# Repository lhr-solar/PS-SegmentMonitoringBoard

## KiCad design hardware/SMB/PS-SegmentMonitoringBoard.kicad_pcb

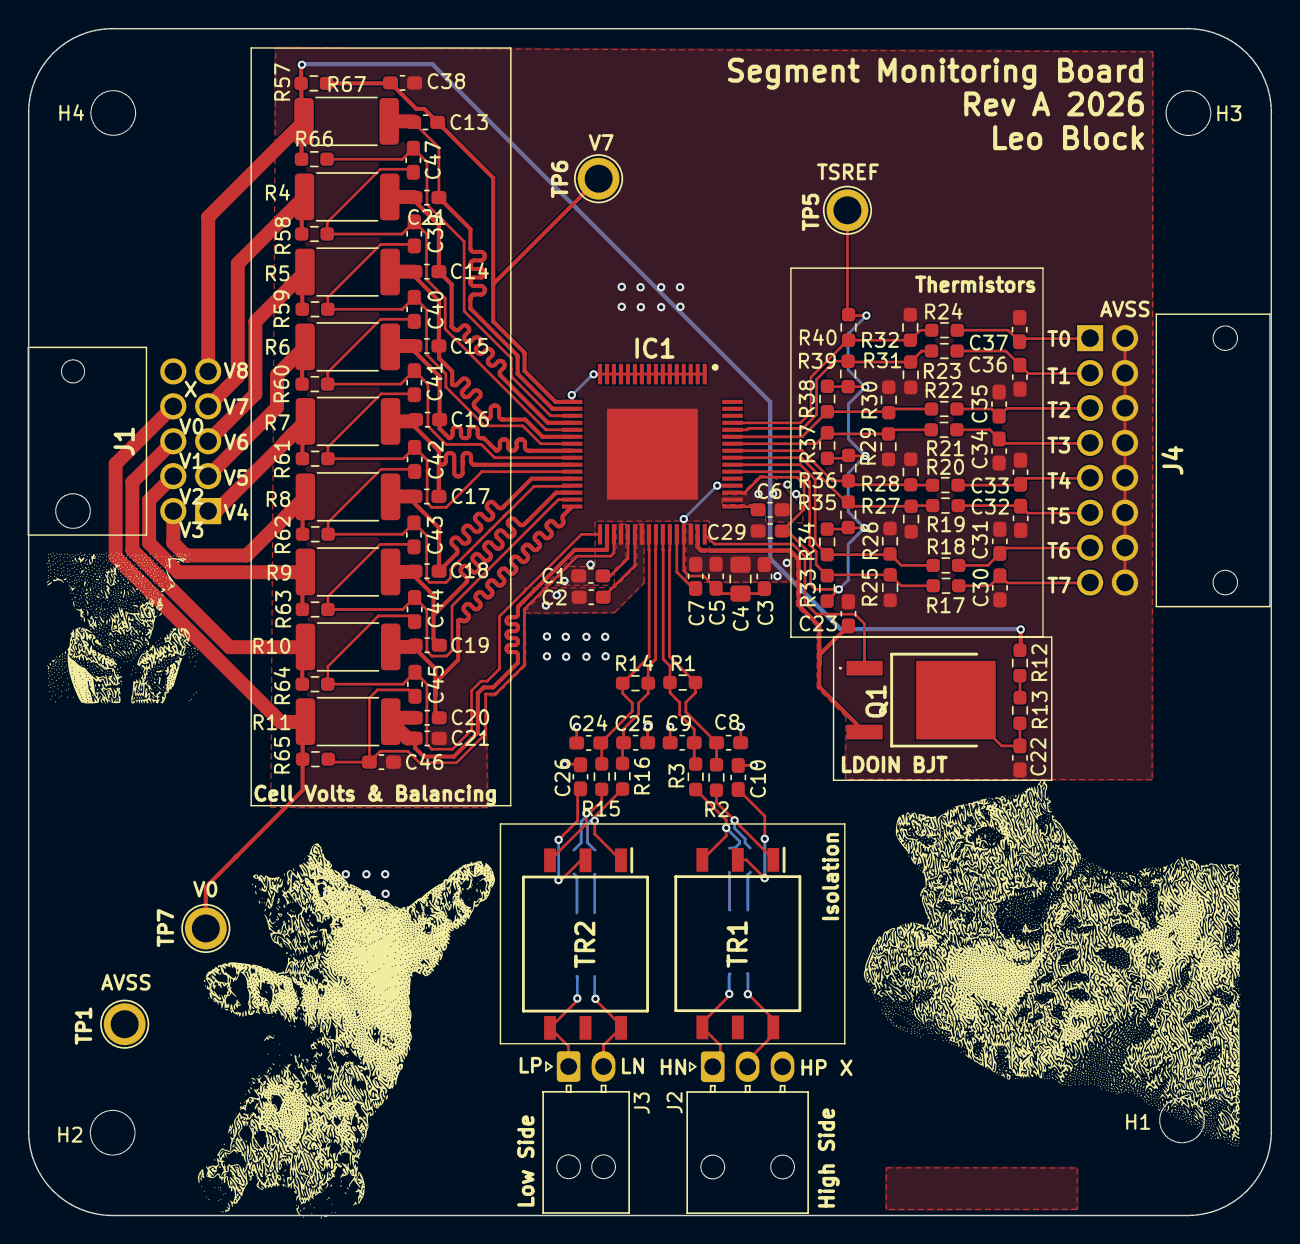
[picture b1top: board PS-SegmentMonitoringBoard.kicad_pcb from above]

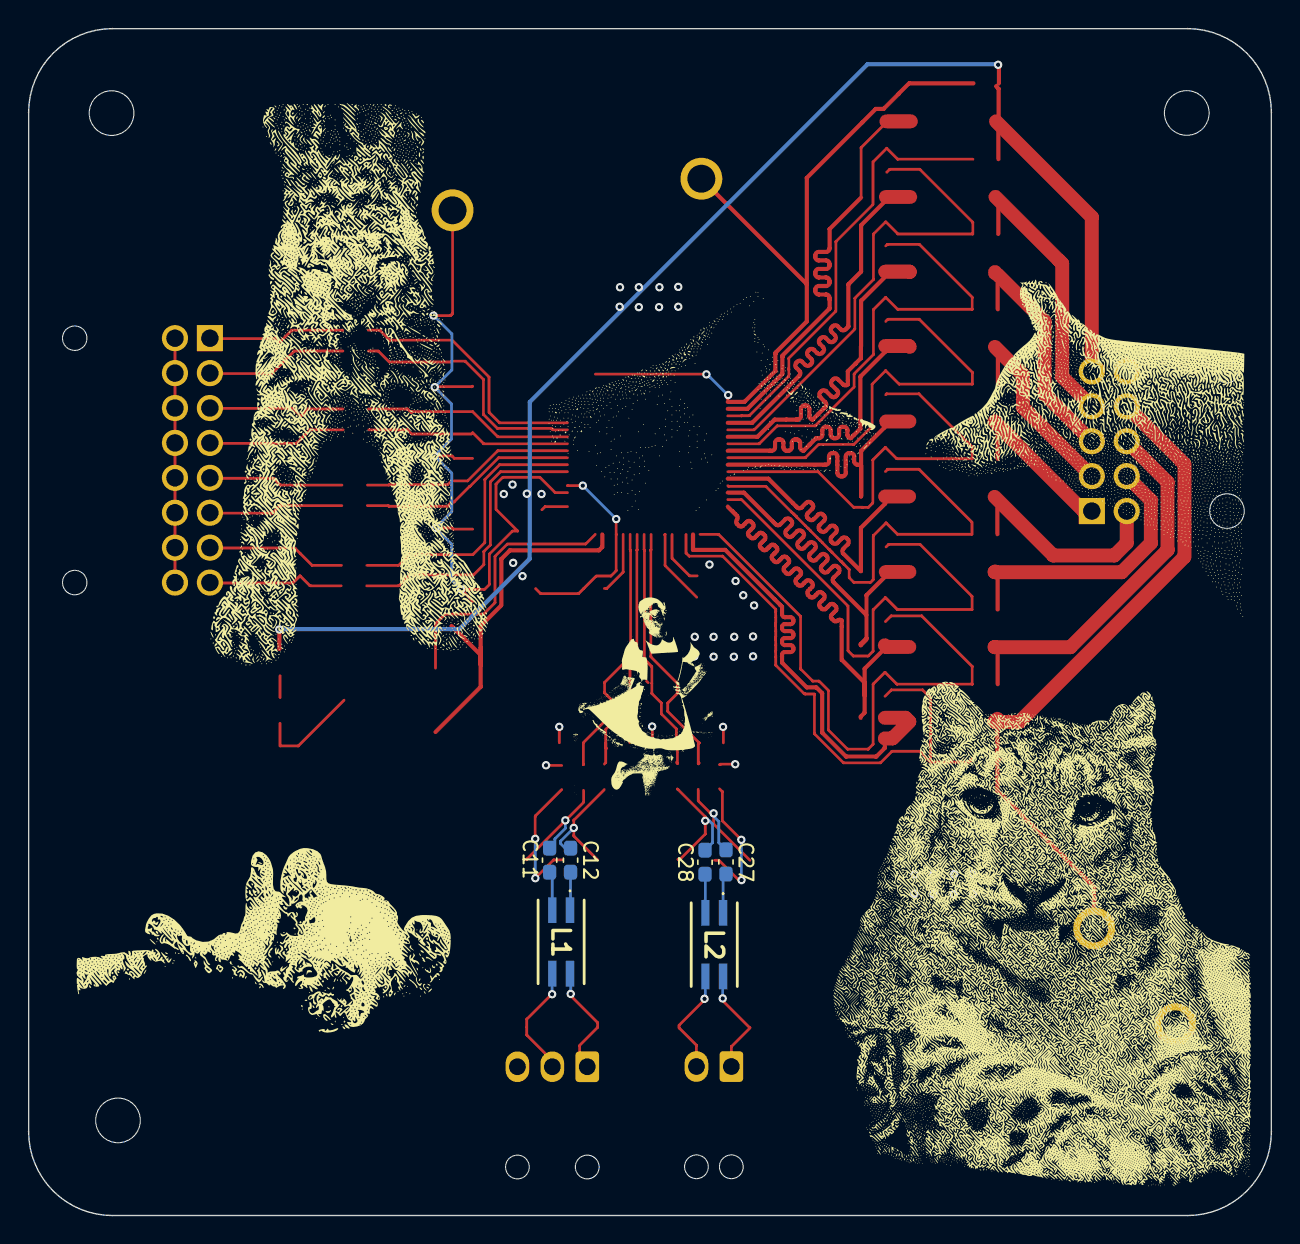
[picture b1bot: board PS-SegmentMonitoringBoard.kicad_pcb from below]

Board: 4 copper layers, 89.0 x 85.0 mm, 118 parts (6 on the bottom side), 73 nets.

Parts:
C1, C2, C29, C30, C31, C32, C33, C34, C35, C36, C37: 1uF; C_0603_1608Metric_Pad1.08x0.95mm_HandSolder
C3: 22nF; C_0603_1608Metric_Pad1.08x0.95mm_HandSolder
C4: 4.7uF; C_0805_2012Metric_Pad1.18x1.45mm_HandSolder
C5: 100nF; C_0603_1608Metric_Pad1.08x0.95mm_HandSolder
C6: 2.2uF; C_0603_1608Metric_Pad1.08x0.95mm_HandSolder
C7, C23: 0.1uF; C_0603_1608Metric_Pad1.08x0.95mm_HandSolder
C8, C9, C11, C12, C24, C25, C27, C28: 220pF; C_0603_1608Metric_Pad1.08x0.95mm_HandSolder
C10, C26: 100pF; C_0603_1608Metric_Pad1.08x0.95mm_HandSolder
C13, C14, C15, C16, C17, C18, C19, C20, C21, C21#2, C39, C40, C41, C42, C43, C44, C45, C46, C47: 0.47uF; C_0603_1608Metric_Pad1.08x0.95mm_HandSolder
C22: 0.22uF; C_0603_1608Metric_Pad1.08x0.95mm_HandSolder
C38: 10nF; C_0603_1608Metric_Pad1.08x0.95mm_HandSolder
H1, H2, H3, H4: MountingHole; MountingHole_3.2mm_M3
IC1: BQ79616PAPR; QFP50P1200X1200X120-65N
J1: voltTapConn; 1053141110
J2: highSideConn; Molex_Nano-Fit_105313-xx03_1x03_P2.50mm_Horizontal
J3: lowSideConn; Molex_Nano-Fit_105313-xx02_1x02_P2.50mm_Horizontal
J4: thermConn; 1053141116
L1, L2: L_Coupled_1423; 744242471
LOGO1: Dr. Hallock; LHRs_LOGO
Q1: ZXTN4004KTC
R1, R14, R17, R18, R19, R20, R21, R22, R23, R24: 1k; R_0603_1608Metric_Pad0.98x0.95mm_HandSolder
R2, R3, R15, R16: 49; R_0603_1608Metric_Pad0.98x0.95mm_HandSolder
R4, R5, R6, R7, R8, R9, R10, R11, R67: 6.2; R_2512_6332Metric_Pad1.40x3.35mm_HandSolder
R12: 200; R_0603_1608Metric_Pad0.98x0.95mm_HandSolder
R13, R58, R59, R60, R61, R62, R63, R64, R65, R66: 100; R_0603_1608Metric_Pad0.98x0.95mm_HandSolder
R25, R26, R27, R28, R29, R30, R31, R32: 15k; R_0603_1608Metric_Pad0.98x0.95mm_HandSolder
R33, R34, R35, R36, R37, R38, R39, R40: 3.6k; R_0603_1608Metric_Pad0.98x0.95mm_HandSolder
R57: 30; R_0603_1608Metric_Pad0.98x0.95mm_HandSolder
TP1: AVSS; TestPoint_Plated_Hole_D2.0mm
TP5: TSREF; TestPoint_Plated_Hole_D2.0mm
TP6: V7; TestPoint_Plated_Hole_D2.0mm
TP7: V0; TestPoint_Plated_Hole_D2.0mm
TR1, TR2: HMU1228NL; SOP254P1270X685-6N

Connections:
/CB0: C20.2, C21.1, IC1.34 (CB0), R11.2
/CB1: C19.2, C20.1, IC1.32 (CB1), R10.2
/CB2: C18.2, C19.1, IC1.30 (CB2), R9.2
/CB3: C17.2, C18.1, IC1.28 (CB3), R8.2
/CB4: C16.2, C17.1, IC1.26 (CB4), R7.2
/CB5: C15.2, C16.1, IC1.24 (CB5), R6.2
/CB6: C14.2, C15.1, IC1.22 (CB6), R5.2
/CB7: C14.1, C21#2.2, IC1.20 (CB7), R4.2
/CB8: C13.2, C21#2.1, IC1.18 (CB8), R67.2
/CVDD: C3.1, C4.1, C5.1, IC1.45 (CVDD), IC1.52 (RX)
/Cell_Balancing/V0: J1.9, R11.1, R65.1, TP7.1 (1_1)
/Cell_Balancing/V1: J1.8, R10.1, R64.1
/Cell_Balancing/V2: J1.7, R9.1, R63.1
/Cell_Balancing/V3: J1.6, R8.1, R62.1
/Cell_Balancing/V4: J1.5, R7.1, R61.1
/Cell_Balancing/V5: J1.4, R6.1, R60.1
/Cell_Balancing/V6: J1.3, R5.1, R59.1
/Cell_Balancing/V7: J1.2, R4.1, R58.1
/Cell_Balancing/V8: J1.1, R12.1, R57.2, R66.1, R67.1
/LDOIN_NPN/LDOIN: C23.1, IC1.47 (LDOIN), Q1.3 (E)
/LDOIN_NPN/NPNB: IC1.48 (NPNB), Q1.1 (B)
/TSREF: C29.1, IC1.51 (TSREF), R33.2, R34.2, R35.2, R36.2, R37.2, R38.2, R39.2, R40.2, TP5.1 (1_1)
/Thermistors/NTC0: IC1.61 (GPIO1), R24.1, R32.2, R40.1
/Thermistors/NTC1: IC1.60 (GPIO2), R23.1, R31.2, R39.1
/Thermistors/NTC2: IC1.59 (GPIO3), R22.1, R30.2, R38.1
/Thermistors/NTC3: IC1.58 (GPIO4), R21.1, R29.2, R37.1
/Thermistors/NTC4: IC1.57 (GPIO5), R20.1, R28.2, R36.1
/Thermistors/NTC5: IC1.56 (GPIO6), R19.1, R27.2, R35.1
/Thermistors/NTC6: IC1.55 (GPIO7), R18.1, R26.2, R34.1
/Thermistors/NTC7: IC1.54 (GPIO8), R17.1, R25.2, R33.1
/Thermistors/TEMP_0: C37.1, J4.8, R24.2
/Thermistors/TEMP_1: C36.1, J4.7, R23.2
/Thermistors/TEMP_2: C35.1, J4.6, R22.2
/Thermistors/TEMP_3: C34.1, J4.5, R21.2
/Thermistors/TEMP_4: C33.1, J4.4, R20.2
/Thermistors/TEMP_5: C32.1, J4.3, R19.2
/Thermistors/TEMP_6: C31.1, J4.2, R18.2
/Thermistors/TEMP_7: C30.1, J4.1, R17.2
/Volt_Taps/VC0: C45.2, C46.1, IC1.35 (VC0), R65.2
/Volt_Taps/VC1: C44.2, C45.1, IC1.33 (VC1), R64.2
/Volt_Taps/VC2: C43.2, C44.1, IC1.31 (VC2), R63.2
/Volt_Taps/VC3: C42.2, C43.1, IC1.29 (VC3), R62.2
/Volt_Taps/VC4: C41.2, C42.1, IC1.27 (VC4), R61.2
/Volt_Taps/VC5: C40.2, C41.1, IC1.25 (VC5), R60.2
/Volt_Taps/VC6: C39.2, C40.1, IC1.23 (VC6), R59.2
/Volt_Taps/VC7: C39.1, C47.2, IC1.21 (VC7), R58.2
/Volt_Taps/VC8: C47.1, IC1.19 (VC8), R66.2
/extraCells: C13.1, C38.2, IC1.1 (BAT), IC1.2 (CB16), IC1.3 (VC16), IC1.4 (CB15), IC1.5 (VC15), IC1.6 (CB14), IC1.7 (VC14), IC1.8 (CB13), IC1.9 (VC13), IC1.10 (CB12), IC1.11 (VC12), IC1.12 (CB11), IC1.13 (VC11), IC1.14 (CB10), IC1.15 (VC10), IC1.16 (CB9), IC1.17 (VC9), R57.1, TP6.1 (1_1)
/highSideIsolation/COMHN: C9.1, IC1.42 (COMHN), R1.2, R3.1
/highSideIsolation/COMHP: C8.1, IC1.43 (COMHP), R1.1, R2.1
/highSideIsolation/isolatedCOMHN: J2.1, L1.4, TR1.4
/highSideIsolation/isolatedCOMHP: J2.2, L1.3, TR1.6
/highSideIsolation/preIsolationCOMHN: C12.1, R3.2, TR1.3
/highSideIsolation/preIsolationCOMHP: C11.1, R2.2, TR1.1
/lowSideIsolation/COMLN: C25.1, IC1.41 (COMLN), R14.2, R16.1
/lowSideIsolation/COMLP: C24.1, IC1.40 (COMLP), R14.1, R15.1
/lowSideIsolation/isolatedCOMLN: J3.2, L2.3, TR2.6
/lowSideIsolation/isolatedCOMLP: J3.1, L2.4, TR2.4
/lowSideIsolation/preIsolationCOMHN: C28.1, R16.2, TR2.1
/lowSideIsolation/preIsolationCOMHP: C27.1, R15.2, TR2.3
AVSS: C1.2, C2.2, C3.2, C4.2, C5.2, C6.2, C7.1, C8.2, C9.2, C10.1, C21.2, C22.2, C23.2, C24.2, C25.2, C26.1, C29.2, C30.2, C31.2, C32.2, C33.2, C34.2, C35.2, C36.2, C37.2, C38.1, C46.2, IC1.36 (REFHM), IC1.39 (AVSS), IC1.46 (CVSS), IC1.50 (DVSS), IC1.65 (PAD), J4.9, J4.10, J4.11, J4.12, J4.13, J4.14, J4.15, J4.16, R25.1, R26.1, R27.1, R28.1, R29.1, R30.1, R31.1, R32.1, TP1.1 (1_1)
unnamed: C10.2, TR1.2
unnamed: C11.2, L1.2
unnamed: C12.2, L1.1
unnamed: C26.2, TR2.2
unnamed: C27.2, L2.1
unnamed: C28.2, L2.2
unnamed: C2.1, IC1.38 (AVDD)
unnamed: C6.1, IC1.49 (DVDD)
unnamed: C7.2, IC1.44 (NEG5V)
unnamed: C1.1, IC1.37 (REFHP)
unnamed: C22.1, Q1.2 (C), R13.2
unnamed: R12.2, R13.1
